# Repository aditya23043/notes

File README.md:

This repo was intended to have all my notes, but with 214 commits, it has reached the 2GB github limit and I cannot push any more commits.
Hence, I will be making separate repositories for different stuff.

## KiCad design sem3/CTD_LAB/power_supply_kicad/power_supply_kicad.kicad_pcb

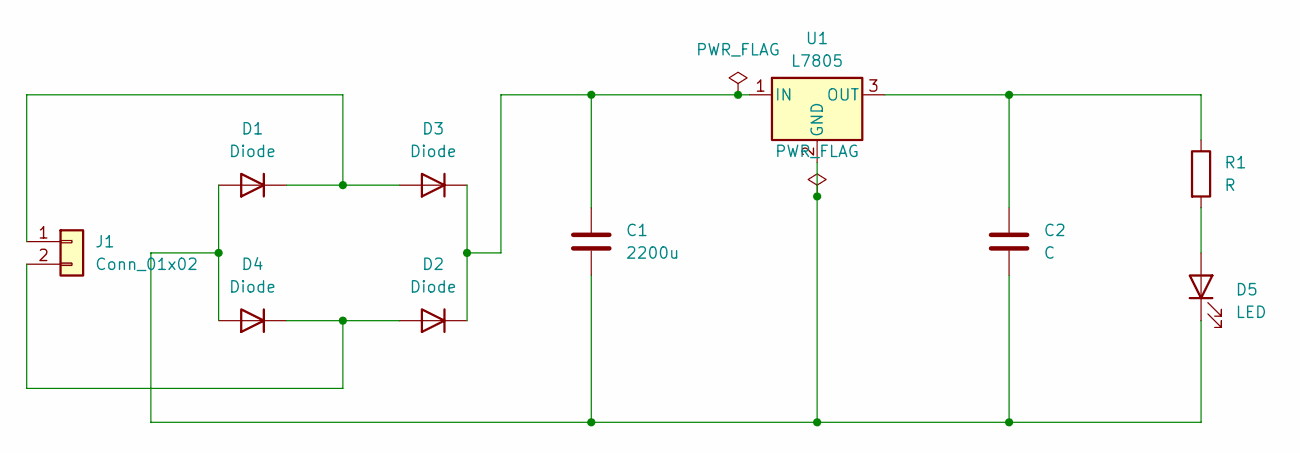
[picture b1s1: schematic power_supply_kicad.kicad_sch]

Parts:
C1: 2200u; CP_Radial_D5.0mm_P2.50mm
C2: C; C_Disc_D8.0mm_W2.5mm_P5.00mm
D1, D2, D3, D4: Diode; D_DO-15_P10.16mm_Horizontal
D5: LED; LED_D3.0mm
J1: Conn_01x02; JWT_A3963_1x02_P3.96mm_Vertical
R1: R; R_Axial_DIN0204_L3.6mm_D1.6mm_P2.54mm_Vertical
U1: L7805; TO-220-3_Horizontal_TabUp

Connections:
unnamed: C1.2, C2.2, D1.2 (A), D4.2 (A), D5.1 (K), U1.2 (GND)
unnamed: D1.1 (K), D3.2 (A), J1.1
unnamed: D2.2 (A), D4.1 (K), J1.2
unnamed: C1.1, D2.1 (K), D3.1 (K), U1.1 (IN)
unnamed: D5.2 (A), R1.2
unnamed: C2.1, R1.1, U1.3 (OUT)

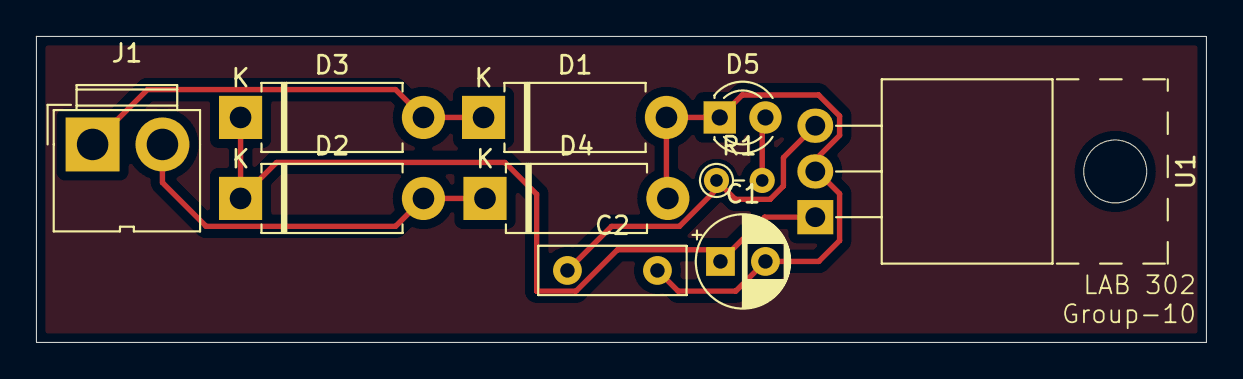
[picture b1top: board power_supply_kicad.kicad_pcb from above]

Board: 2 copper layers, 65.0 x 17.0 mm, 10 parts (0 on the bottom side), 6 nets.

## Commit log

2024-03-17 something
2024-03-18 sofmsd
2024-03-18 restored
2024-03-19 19_03_24
2024-03-20 Added opengl notes
2024-03-24 co and dsa notes were updated earlier but not commited
2024-03-24 EBOs done and formatted the code in a better way
2024-03-25 25_03_24
2024-03-25 SHADER: Different colors on different vertices by changing VBO memory and adding color attribute to vertex attibutes
2024-03-26 defined the shader class in shader.h header file
2024-03-31 Texture: beginning
2024-03-31 Added dots
2024-03-31 Added dots for suckless programs
2024-03-31 test
2024-03-31 st done
2024-04-02 2_03_24
2024-04-02 prev yr pns notes
2024-04-02 pns notes prev
2024-04-05 dots
2024-04-05 st dots
2024-04-06 CO notes
2024-04-08 co project
2024-04-09 Added wayland dots
2024-04-10 wl dots
2024-04-12 CO notes updated and BE sec B notes added
2024-04-18 CO classes
2024-04-18 18_04_24
2024-04-18 Added my archinstall script
2024-04-18 Added mako config
2024-04-22 updated dots
2024-04-22 added packages.conf
2024-04-22 added git and fish as packages
2024-04-25 notes updated
2024-04-26 Isa notes updated
2024-05-04 Arch setup
2024-05-04 dosfstools
2024-05-04 touchpad
2024-05-04 chromium flags
2024-05-21 updated dots:
2024-05-22 nvim updated to multi file conf style
2024-05-30 Dots updated
2024-07-25 Updated wireless keyboard firmware
2024-08-18 Create LICENSE
2024-08-27 Updated Dots after switching
2024-08-30 Went from java to c to cpp to asm to javascript and now finally to HTMX + GO in a single commit demn
2024-08-31 Added write
2024-09-01 V241eak Commit: sns.pdf, sns_lectures, sns_revision.pdf
2024-09-02 a15: sns_rev ctd sns_assignment
2024-09-03 a15: LAB 3 ELD
2024-09-03 ELD LAB
2024-09-03 LAB3 ELD FINAL
2024-09-03 ELD LAB FINAL FROM ASUS TUFA15
2024-09-04 AP NOTES: asus tuf a15
2024-09-05 05/09/24 asus
2024-09-06 asus
2024-09-07 v241eak
2024-09-09 tuf15
2024-09-10 tuf a15
2024-09-12 Bha birthday flutter completed
2024-09-12 asus tuf a15
2024-09-18 pushed sns notes
2024-09-20 sns notes
2024-09-21 asus tuf a1%
2024-09-24 pushed ctd notes from lec 11
2024-09-24 removed private docs
2024-09-26 ELD notes pushes
2024-09-30 ELD BRAM Notes pushed
2024-10-01 sdl in c notes
2024-10-03 trying to prevent a lawsuit
2024-10-04 soemthing
2024-10-05 ELD exam stuff
2024-10-08 AP notes
2024-10-08 removed confidential stuff
2024-10-14 CTD Notes
2024-10-15 eld notes
2024-10-16 vim clipboard working finally yooo!!!
2024-10-17 ELD notes pushed
2024-11-06 A lot of stuff updated in this commit, including, but not limited to: rust, ELD lab 8, haskell, cmake
2024-11-13 ap notes pushed
2024-11-14 sns, eld, ctd notes updated
2024-11-17 ctd notes pushed for quiz revision
2024-11-19 pushed ELD notes
2024-11-22 ludo project wip
2024-11-28 added mac info
2025-01-07 removed large files
2025-01-12 sem4 dots updated
2025-01-20 sem4 stuff updated
